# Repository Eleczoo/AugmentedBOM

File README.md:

# Augmented BOM (Lauzhack 2022 project)
This project is inspired by [InspectAR](https://www.inspectar.com/). The goal is to allow people to **mount**, **toubleshoot** and **inspect** PCBs with ease by showing them what they need in augmented Reality. We've decided to embed the video feed into an already existing web Tool: [Interactive BOM for KiCad.
](https://github.com/openscopeproject/InteractiveHtmlBom). This tool allows us to sort, select, name and filter specific nets, components etc.

> Note: This project has been done as a group of 3 students in only 2 days at the Lauzhack (EPFL Hackathon).

## Demo

## How does it work
In order to get the selected nets and plans from the PCB into a video feed in augmented reality, we've implemented a simple pipeline:
1. `Calibration` : The user gets the board under the camera and put points on the corners of the board (This allows a better edge detection)  
2. `Data extraction` : We Extract selected nets, pads and plans of the PCB from Interactive BOM and Send them to a python server.
3. `Get video feed` : From the server, we get the original video stream of only the PCB from the camera. 
4. `Image warping` : Still on the server, we adapt the nets and pads to the angle and distance of the PCB to fit well.
5. `Merge and send` : We merge the fitted nets and the original video feed into a single feed and send it to the Interactive BOM to show it.

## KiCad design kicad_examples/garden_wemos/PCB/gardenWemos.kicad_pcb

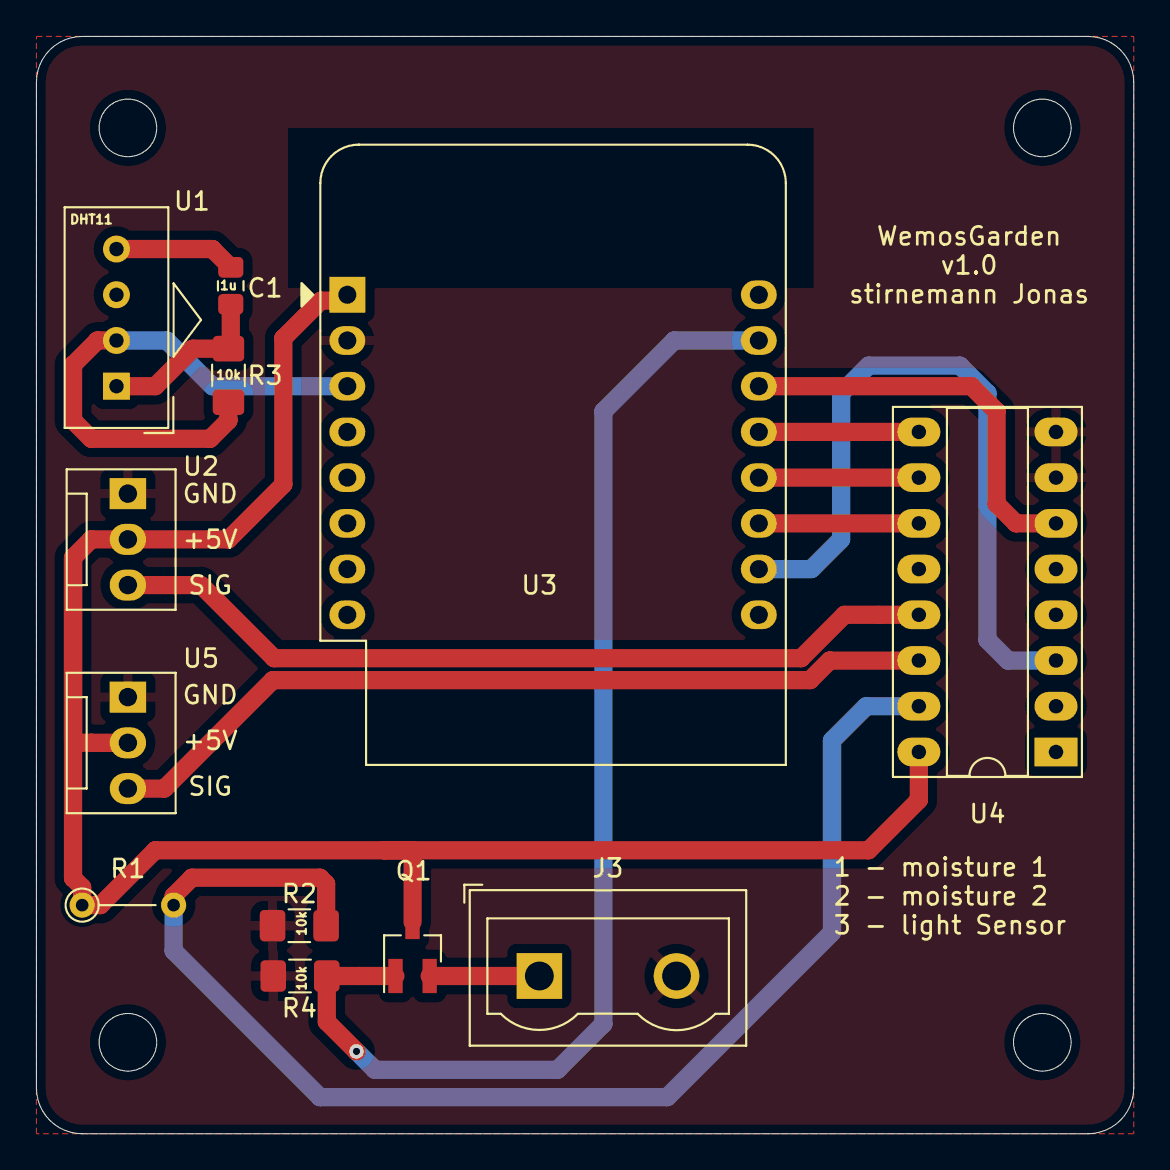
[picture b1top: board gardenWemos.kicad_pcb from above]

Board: 2 copper layers, 61.0 x 61.0 mm, 12 parts (0 on the bottom side), 15 nets.

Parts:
C1: 1u; C_0805_2012Metric_Pad1.15x1.40mm_HandSolder
J3: Screw_Terminal_01x02; TerminalBlock_Wuerth_691311400102_P7.62mm
Q1: NTR4003NT1G; SOT-23_Handsoldering
R1: PHOTO.R; R_Axial_DIN0204_L3.6mm_D1.6mm_P5.08mm_Vertical
R2, R3, R4: 10k; R_1206_3216Metric_Pad1.42x1.75mm_HandSolder
U1: DHT11; Aosong_DHT11_5.5x12.0_P2.54mm
U2, U5: MoistSensor; Fan_Pin_Header_Straight_1x03
U3: WeMos_mini; WEMOS_D1_mini_light
U4: 4051; DIP-16_W7.62mm_Socket_LongPads

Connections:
+5V: Q1.3, R1.1, U2.2, U3.1, U4.16, U5.2
/A: U3.11, U4.11
/AnalogInput: U3.10, U4.3
/B: U3.12, U4.10
/C: U3.13, U4.9
/IO_DHT: R3.2, U1.2, U3.3
/LightOut: R1.2, R2.1, U4.15
/Moisture1: U2.3, U4.13
/Moisture2: U4.14, U5.3
/WaterPump: Q1.1, R4.1, U3.15
/inh: U3.14, U4.6
GND: J3.2, R2.2, R4.2, U2.1, U3.2, U4.7, U4.8, U5.1
unnamed: C1.1, R3.1, U1.1
unnamed: C1.2, U1.4
unnamed: J3.1, Q1.2

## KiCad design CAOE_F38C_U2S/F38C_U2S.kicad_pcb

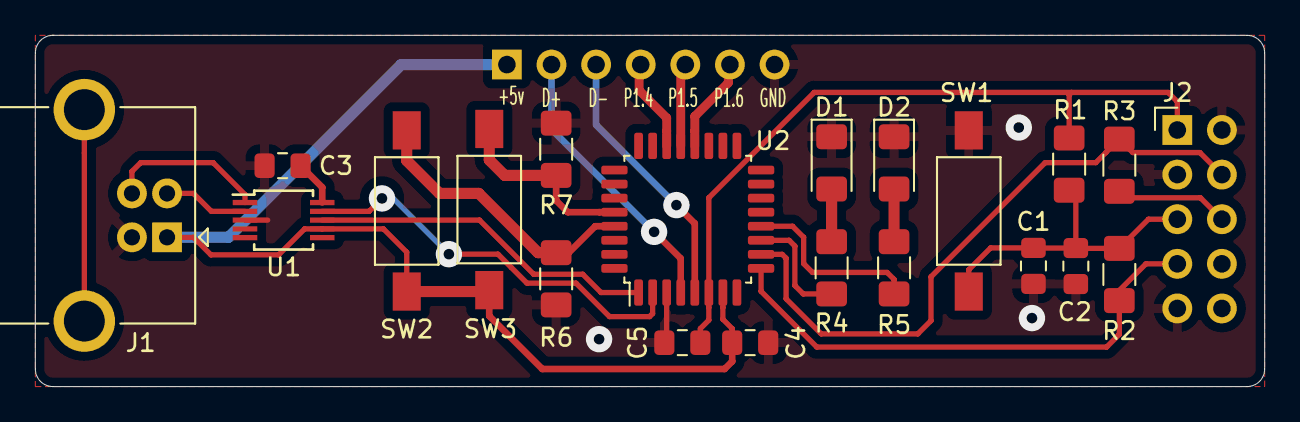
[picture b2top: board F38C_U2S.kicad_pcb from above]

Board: 2 copper layers, 70.0 x 20.0 mm, 22 parts (1 on the bottom side), 23 nets.

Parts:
C1, C3, C4, C5: 0.1u; C_0805_2012Metric_Pad1.15x1.40mm_HandSolder
C2: 1u; C_0805_2012Metric_Pad1.15x1.40mm_HandSolder
D1, D2: LED; LED_1206_3216Metric_Pad1.42x1.75mm_HandSolder
J1: USB_B; USB_B_OST_USB-B1HSxx_Horizontal
J2: Conn_02x05_Odd_Even; PinHeader_2x05_P2.54mm_Horizontal
J3: Conn_01x07_Male; PinHeader_1x07_P2.54mm_Vertical
R1, R2, R3, R4, R5: 1k; R_1206_3216Metric_Pad1.42x1.75mm_HandSolder
R6, R7: 10k; R_1206_3216Metric_Pad1.42x1.75mm_HandSolder
SW1, SW2, SW3: SW_Push; SW_SPST_FSMSM
U1: CH340E; MSOP-10_3x3mm_P0.5mm
U2: 8051F38C; LQFP-32_7x7mm_P0.8mm

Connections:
+3V3: C5.1, J2.1, R1.1, U2.6
+5V: C4.1, J1.1, J3.1, SW2.2, SW3.2, U1.7, U2.7
/C2D: J2.4, R3.1, U2.10
/D+: J1.3, U1.1
/D+_uC: J3.2, U2.4
/D-: J1.2, U1.2
/D-_uC: J3.3, U2.5
/JTAG_5: C1.1, C2.1, J2.5, R1.2, R2.2, SW1.2
/JTAG_7: J2.7, R2.1, U2.9
/P0.5: R6.2, SW2.1, U2.29
/P0.6: R7.2, SW3.1, U2.28
/P1.4: J3.4, U2.22
/P1.5: J3.5, U2.21
/P1.6: J3.6, U2.20
/P2.6: R5.2, U2.12
/P2.7: R4.2, U2.11
/RX1: U1.8, U2.1
/RXD: U1.9, U2.2
GND: C1.2, C2.2, C3.2, C4.2, C5.2, D1.1, D2.1, J1.4, J2.2, J2.3, J2.9, J3.7, R6.1, R7.1, SW1.1, U1.3, U2.3
unnamed: C3.1, U1.10
unnamed: D1.2, R4.1
unnamed: D2.2, R5.1
unnamed: J2.6, R3.2

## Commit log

2022-12-03 Added PCB
2022-12-03 Create Server folder
2022-12-03 Added base stream from phone
2022-12-03 created funcs
2022-12-03 Added feed test in main
2022-12-03 Get json file in Server
2022-12-03 Added modification for the js file
2022-12-03 Generated netlist with tracks, added flask app.run
2022-12-03 removed pycache
2022-12-03 remove debug stuff in server
2022-12-03 Working live feed web page
2022-12-03 Modified ibom.html
2022-12-03 Added .gitignore
2022-12-03 Finished drawing edgecuts
2022-12-03 Finished tracks drawing
2022-12-03 Working crop with user clicks
2022-12-03 Added the image of the circuit
2022-12-03 AR not really working
2022-12-03 test
2022-12-03 lots test
2022-12-03 backups i guess
2022-12-04 Crashing when resizing
2022-12-04 Finished footpring drawing
2022-12-04 Kinda working
2022-12-04 Send net name
2022-12-04 Sending nets to flask server
2022-12-04 Fused two flask server
2022-12-04 Draw work from flask server
2022-12-04 More integration done
2022-12-04 Bordel
2022-12-04 Working net selector
2022-12-04 Everything seems to be working fine
2022-12-04 Cleaned a bit
2022-12-04 Added image
2023-02-07 Added some stuff to readme
2023-09-30 Cleaned up and deleted lots of stuff
2024-04-02 cleaned some stuff, added auto pcb detection
2024-04-02 flag redraw seems to not be working
